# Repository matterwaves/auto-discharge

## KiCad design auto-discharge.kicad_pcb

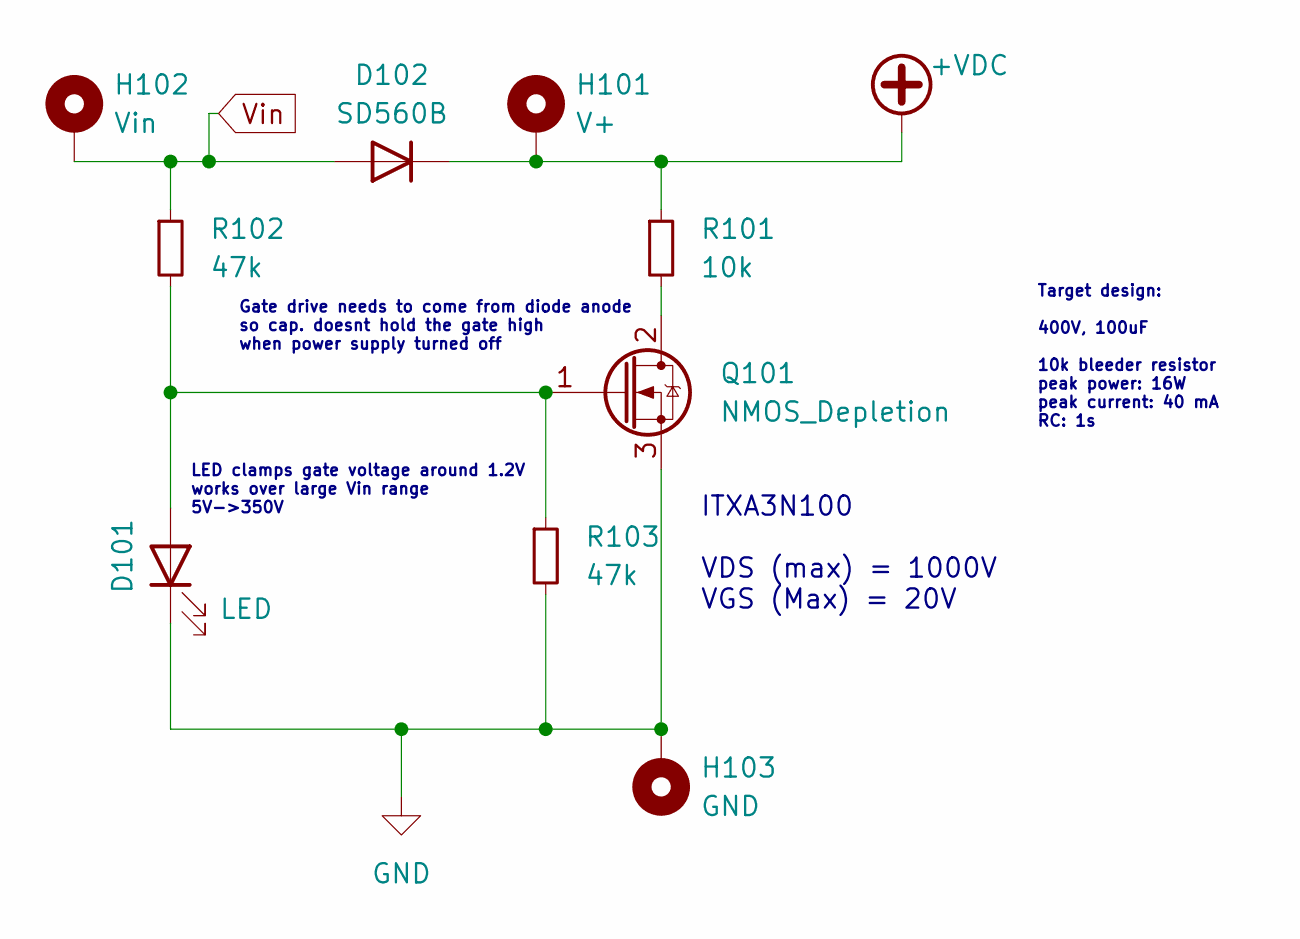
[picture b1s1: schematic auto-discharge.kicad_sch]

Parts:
D101: LED; LED_D5.0mm
D102: SD560B; D_SMA-SMB_Universal_Handsoldering; digikey 1655-SD560BCT-ND
H101: V+; MountingHole_8.4mm_M8_Pad_TopBottom
H102: Vin; MountingHole_8.4mm_M8_Pad_TopBottom
H103: GND; MountingHole_8.4mm_M8_Pad_TopBottom
Q101: NMOS_Depletion; TO-263-2; digikey IXTA3N100D2HV-ND
R101: 10k; R_2512_6332Metric; digikey CHP2512-JW-103ELFTR-ND
R102, R103: 47k; R_0603_1608Metric

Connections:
+VDC: D102.1 (K), H101.1, R101.1
GND: D101.1 (K), H103.1, Q101.3 (S), R103.2
unnamed: D101.2 (A), Q101.1 (G), R102.2, R103.1
unnamed: Q101.2 (D), R101.2
Vin: D102.2 (A), H102.1, R102.1

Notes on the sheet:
LED clamps gate voltage around 1.2V works over large Vin range 5V->350V
ITXA3N100 VDS (max) = 1000V VGS (Max) = 20V
Gate drive needs to come from diode anode so cap. doesnt hold the gate high when power supply turned off
Target design: 400V, 100uF 10k bleeder resistor peak power: 16W peak current: 40 mA RC: 1s

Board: 2 copper layers, 9 parts (0 on the bottom side), 5 nets, no tracks yet.

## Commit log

2024-09-11 init commit
2024-09-15 design flaw fix: pmos instead of depletion mode
